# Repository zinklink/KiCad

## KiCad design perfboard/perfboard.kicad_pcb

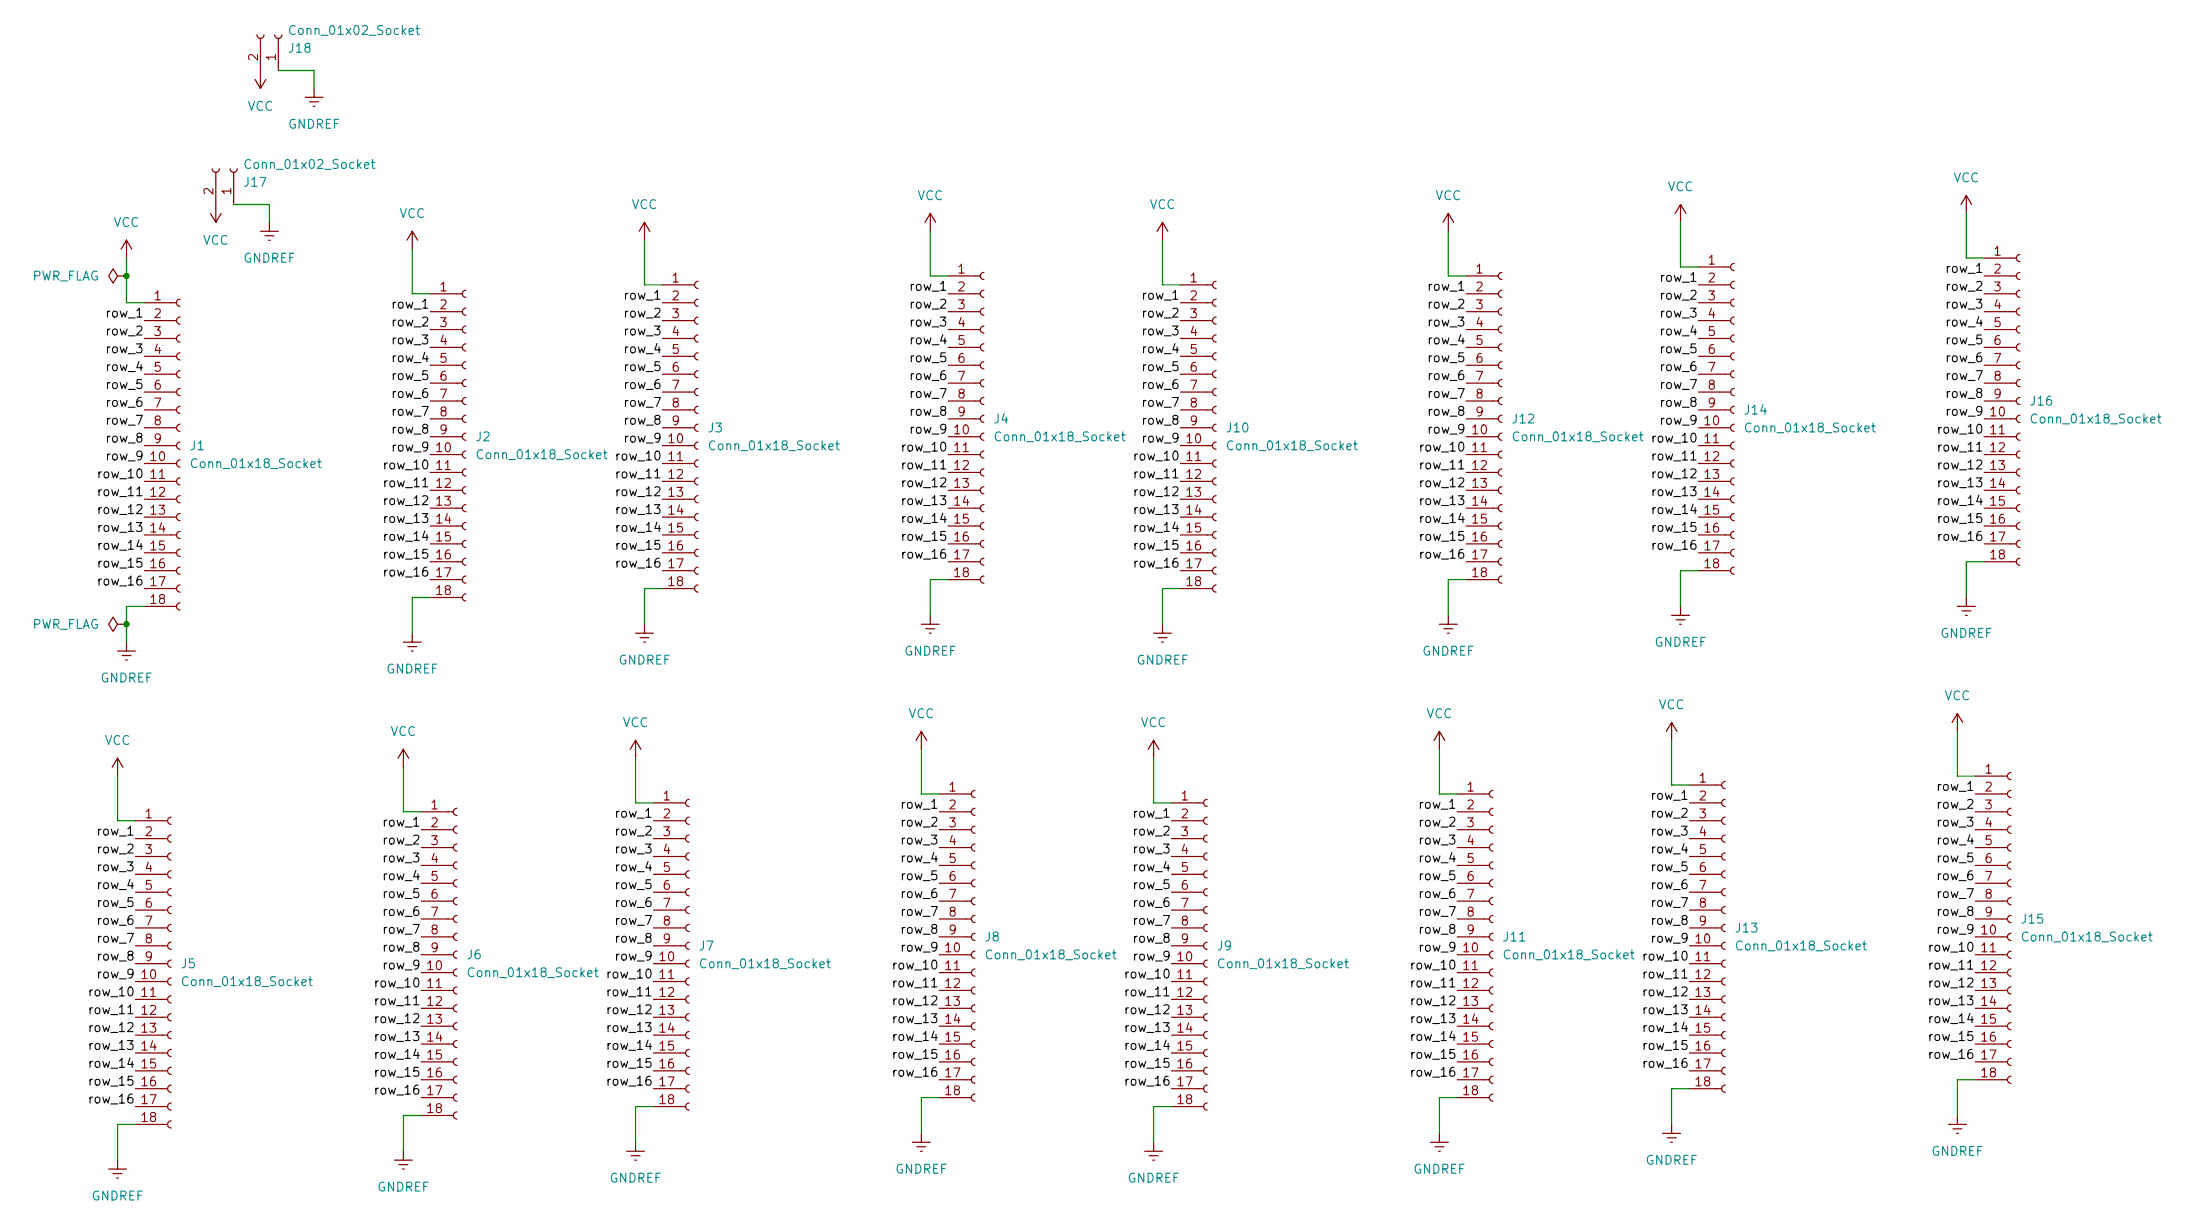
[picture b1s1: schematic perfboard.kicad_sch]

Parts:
J1, J2, J3, J4, J5, J6, J7, J8, J9, J10, J11, J12, J13, J14, J15, J16: Conn_01x18_Socket; PinHeader_1x18_P2.54mm_Vertical
J17, J18: Conn_01x02_Socket; PinHeader_1x02_P2.54mm_Vertical

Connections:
/row_1: J1.2, J2.2, J3.2, J4.2, J5.2, J6.2, J7.2, J8.2, J9.2, J10.2, J11.2, J12.2, J13.2, J14.2, J15.2, J16.2
/row_2: J1.3, J2.3, J3.3, J4.3, J5.3, J6.3, J7.3, J8.3, J9.3, J10.3, J11.3, J12.3, J13.3, J14.3, J15.3, J16.3
/row_3: J1.4, J2.4, J3.4, J4.4, J5.4, J6.4, J7.4, J8.4, J9.4, J10.4, J11.4, J12.4, J13.4, J14.4, J15.4, J16.4
/row_4: J1.5, J2.5, J3.5, J4.5, J5.5, J6.5, J7.5, J8.5, J9.5, J10.5, J11.5, J12.5, J13.5, J14.5, J15.5, J16.5
/row_5: J1.6, J2.6, J3.6, J4.6, J5.6, J6.6, J7.6, J8.6, J9.6, J10.6, J11.6, J12.6, J13.6, J14.6, J15.6, J16.6
/row_6: J1.7, J2.7, J3.7, J4.7, J5.7, J6.7, J7.7, J8.7, J9.7, J10.7, J11.7, J12.7, J13.7, J14.7, J15.7, J16.7
/row_7: J1.8, J2.8, J3.8, J4.8, J5.8, J6.8, J7.8, J8.8, J9.8, J10.8, J11.8, J12.8, J13.8, J14.8, J15.8, J16.8
/row_8: J1.9, J2.9, J3.9, J4.9, J5.9, J6.9, J7.9, J8.9, J9.9, J10.9, J11.9, J12.9, J13.9, J14.9, J15.9, J16.9
/row_9: J1.10, J2.10, J3.10, J4.10, J5.10, J6.10, J7.10, J8.10, J9.10, J10.10, J11.10, J12.10, J13.10, J14.10, J15.10, J16.10
/row_10: J1.11, J2.11, J3.11, J4.11, J5.11, J6.11, J7.11, J8.11, J9.11, J10.11, J11.11, J12.11, J13.11, J14.11, J15.11, J16.11
/row_11: J1.12, J2.12, J3.12, J4.12, J5.12, J6.12, J7.12, J8.12, J9.12, J10.12, J11.12, J12.12, J13.12, J14.12, J15.12, J16.12
/row_12: J1.13, J2.13, J3.13, J4.13, J5.13, J6.13, J7.13, J8.13, J9.13, J10.13, J11.13, J12.13, J13.13, J14.13, J15.13, J16.13
/row_13: J1.14, J2.14, J3.14, J4.14, J5.14, J6.14, J7.14, J8.14, J9.14, J10.14, J11.14, J12.14, J13.14, J14.14, J15.14, J16.14
/row_14: J1.15, J2.15, J3.15, J4.15, J5.15, J6.15, J7.15, J8.15, J9.15, J10.15, J11.15, J12.15, J13.15, J14.15, J15.15, J16.15
/row_15: J1.16, J2.16, J3.16, J4.16, J5.16, J6.16, J7.16, J8.16, J9.16, J10.16, J11.16, J12.16, J13.16, J14.16, J15.16, J16.16
/row_16: J1.17, J2.17, J3.17, J4.17, J5.17, J6.17, J7.17, J8.17, J9.17, J10.17, J11.17, J12.17, J13.17, J14.17, J15.17, J16.17
GNDREF: J1.18, J2.18, J3.18, J4.18, J5.18, J6.18, J7.18, J8.18, J9.18, J10.18, J11.18, J12.18, J13.18, J14.18, J15.18, J16.18, J17.1, J18.1
VCC: J1.1, J2.1, J3.1, J4.1, J5.1, J6.1, J7.1, J8.1, J9.1, J10.1, J11.1, J12.1, J13.1, J14.1, J15.1, J16.1, J17.2, J18.2

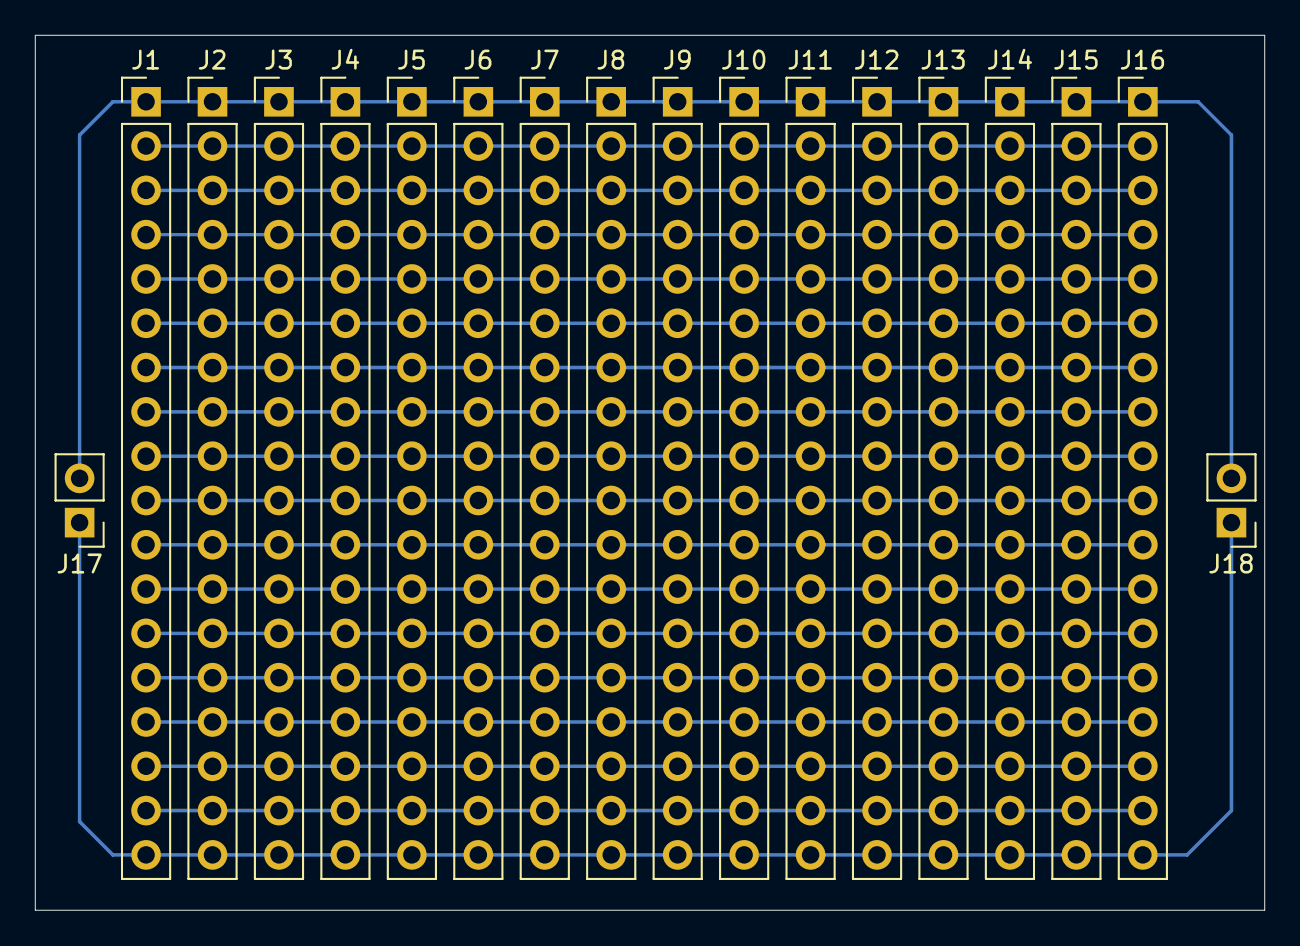
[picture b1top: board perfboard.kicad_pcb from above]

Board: 2 copper layers, 70.5 x 50.2 mm, 18 parts (0 on the bottom side), 18 nets.

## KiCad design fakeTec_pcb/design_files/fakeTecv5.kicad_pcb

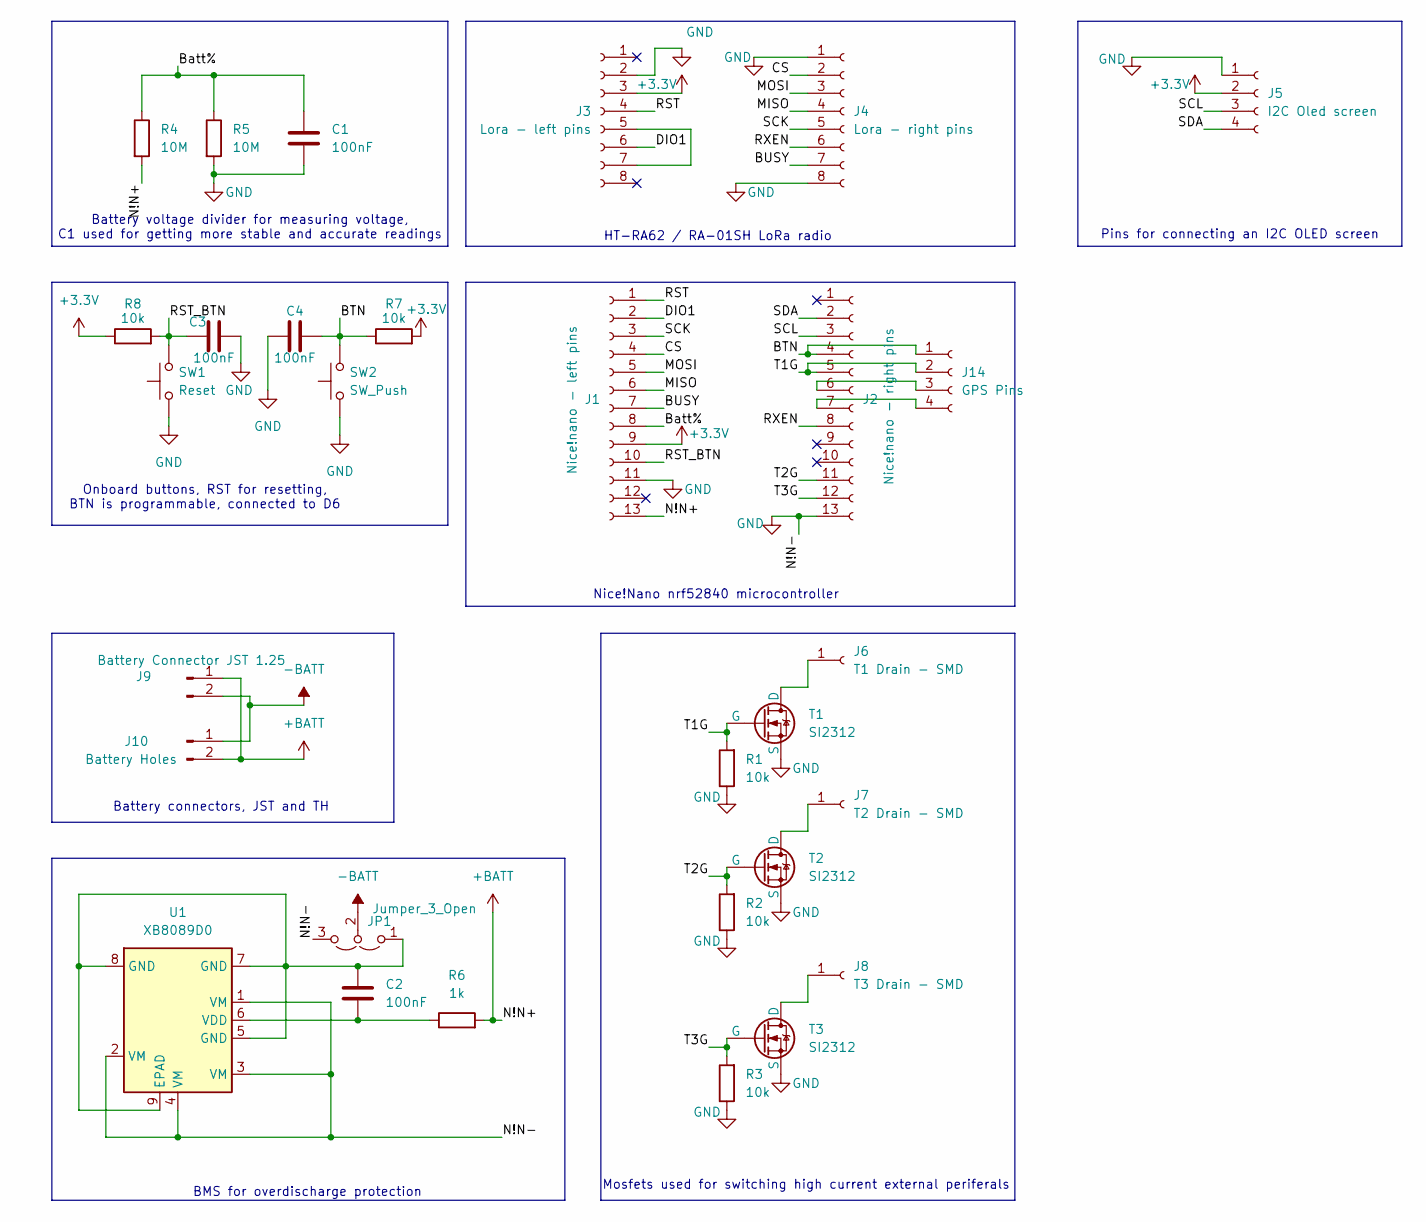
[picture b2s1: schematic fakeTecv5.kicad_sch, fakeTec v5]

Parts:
C1, C2, C3, C4: 100nF; C_1206_3216Metric_Pad1.33x1.80mm_HandSolder
J1: Nice!nano - left pins; SMD_Pad_Row_P2.54_13x1
J2: Nice!nano - right pins; SMD_Pad_Row_P2.54_13x1
J3: Lora - left pins; SMD_Pad_Row_P2.00_8x1_longer
J4: Lora - right pins; SMD_Pad_Row_P2.00_8x1
J5: I2C Oled screen; PinHeader_1x04_P2.54mm_Vertical
J6: T1 Drain - SMD; SMD_PAD_1x1
J7: T2 Drain - SMD; SMD_PAD_1x1
J8: T3 Drain - SMD; SMD_PAD_1x1
J9: Battery Connector JST 1.25; JST_GH_SM02B-GHS-TB_1x02-1MP_P1.25mm_Horizontal
J10: Battery Holes; PinHeader_1x02_P2.54mm_Vertical
J14: GPS Pins; SMD_PAD_4x1
JP1: Jumper_3_Open; SolderJumper-3_P1.3mm_Open_RoundedPad1.0x1.5mm
R1, R2, R3, R7, R8: 10k; R_1206_3216Metric_Pad1.30x1.75mm_HandSolder
R4, R5: 10M; R_1206_3216Metric_Pad1.30x1.75mm_HandSolder
R6: 1k; R_1206_3216Metric_Pad1.30x1.75mm_HandSolder
SW1: Reset; SW_Push_SPST_NO_Alps_SKRK
SW2: SW_Push; SW_Push_SPST_NO_Alps_SKRK
T1, T2, T3: SI2312; TSOT-23_HandSoldering_Updated
U1: XB8089D0; SOIC-8-1EP_3.9x4.9mm_P1.27mm_EP2.41x3.3mm

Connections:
+3.3V: J1.9, J3.3, J5.2, R7.2, R8.1
+BATT: J1.13, J9.1, J10.2, R4.2, R6.2
-BATT: J9.2, J10.1, JP1.2 (C)
/BTN: C4.2, J2.4, J14.1, R7.1, SW2.2
/BUSY: J1.7, J4.7
/Batt%: C1.1, J1.8, R4.1, R5.1
/CS: J1.4, J4.2
/DIO1: J1.2, J3.6
/MISO: J1.6, J4.4
/MOSI: J1.5, J4.3
/RST: J1.1, J3.4
/RST_BTN: C3.1, J1.10, R8.2, SW1.2
/RXEN: J2.8, J4.6
/SCK: J1.3, J4.5
/SCL: J2.3, J5.3
/SDA: J2.2, J5.4
/T1G: J2.5, J14.2, R1.2, T1.2 (G)
/T2G: J2.11, R2.2, T2.2 (G)
/T3G: J2.12, R3.2, T3.2 (G)
GND: C1.2, C3.2, C4.1, J1.11, J2.13, J3.2, J4.1, J4.8, J5.1, JP1.3 (B), R1.1, R2.1, R3.1, R5.2, SW1.1, SW2.1, T1.3 (S), T2.3 (S), T3.3 (S), U1.1 (VM), U1.2 (VM), U1.3 (VM), U1.4 (VM)
unnamed: J3.5, J3.7
unnamed: J6.1, T1.1 (D)
unnamed: J7.1, T2.1 (D)
unnamed: J8.1, T3.1 (D)
unnamed: J2.6, J14.3
unnamed: J2.7, J14.4
unnamed: C2.1, JP1.1 (A), U1.5 (GND), U1.7 (GND), U1.8 (GND), U1.9 (EPAD)
unnamed: C2.2, R6.1, U1.6 (VDD)

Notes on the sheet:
Nice!Nano nrf52840 microcontroller
Mosfets used for switching high current external periferals
BMS for overdischarge protection
Battery voltage divider for measuring voltage, C1 used for getting more stable and accurate readings
HT-RA62 / RA-01SH LoRa radio
Onboard buttons, RST for resetting, BTN is programmable, connected to D6
Battery connectors, JST and TH
Pins for connecting an I2C OLED screen

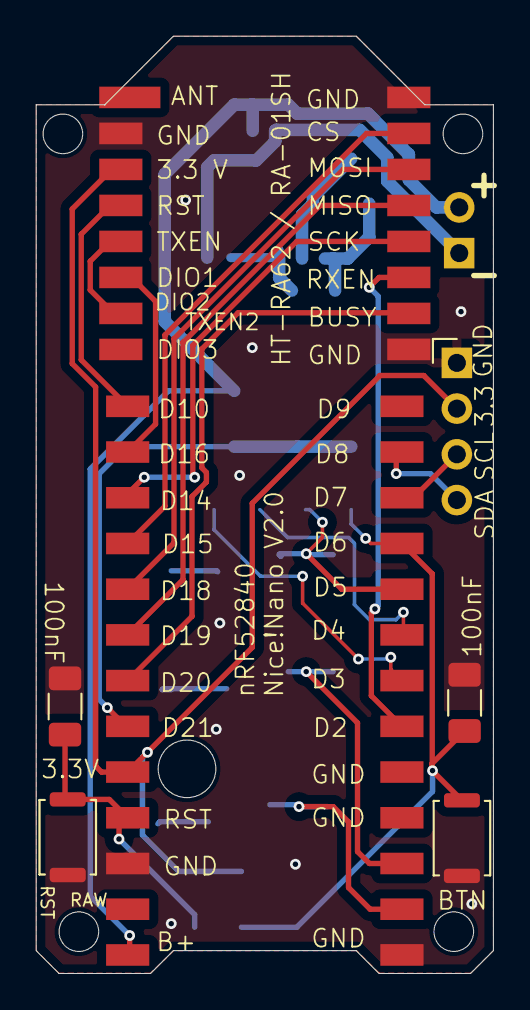
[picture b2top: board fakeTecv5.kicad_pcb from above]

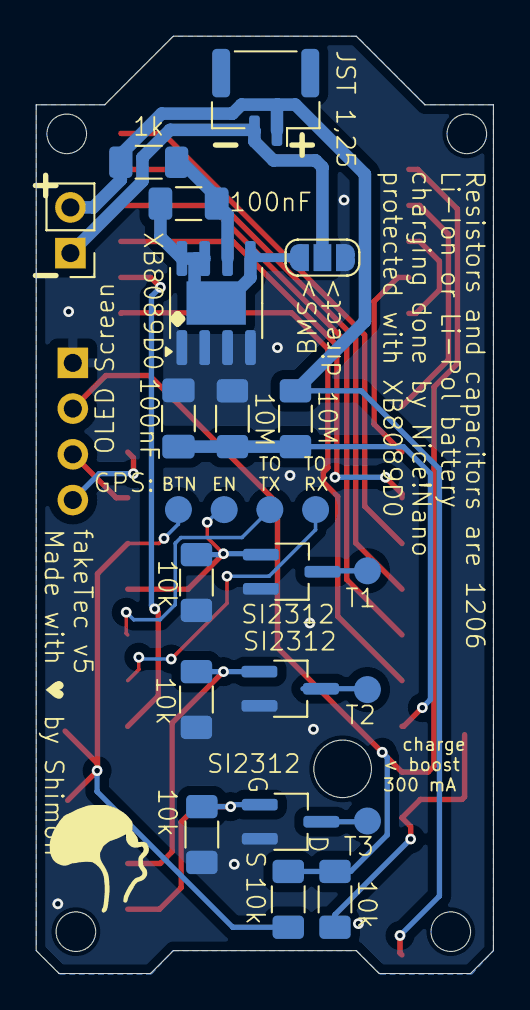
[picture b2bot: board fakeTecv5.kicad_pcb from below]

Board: 2 copper layers, 25.4 x 52.1 mm, 30 parts (21 on the bottom side), 28 nets.

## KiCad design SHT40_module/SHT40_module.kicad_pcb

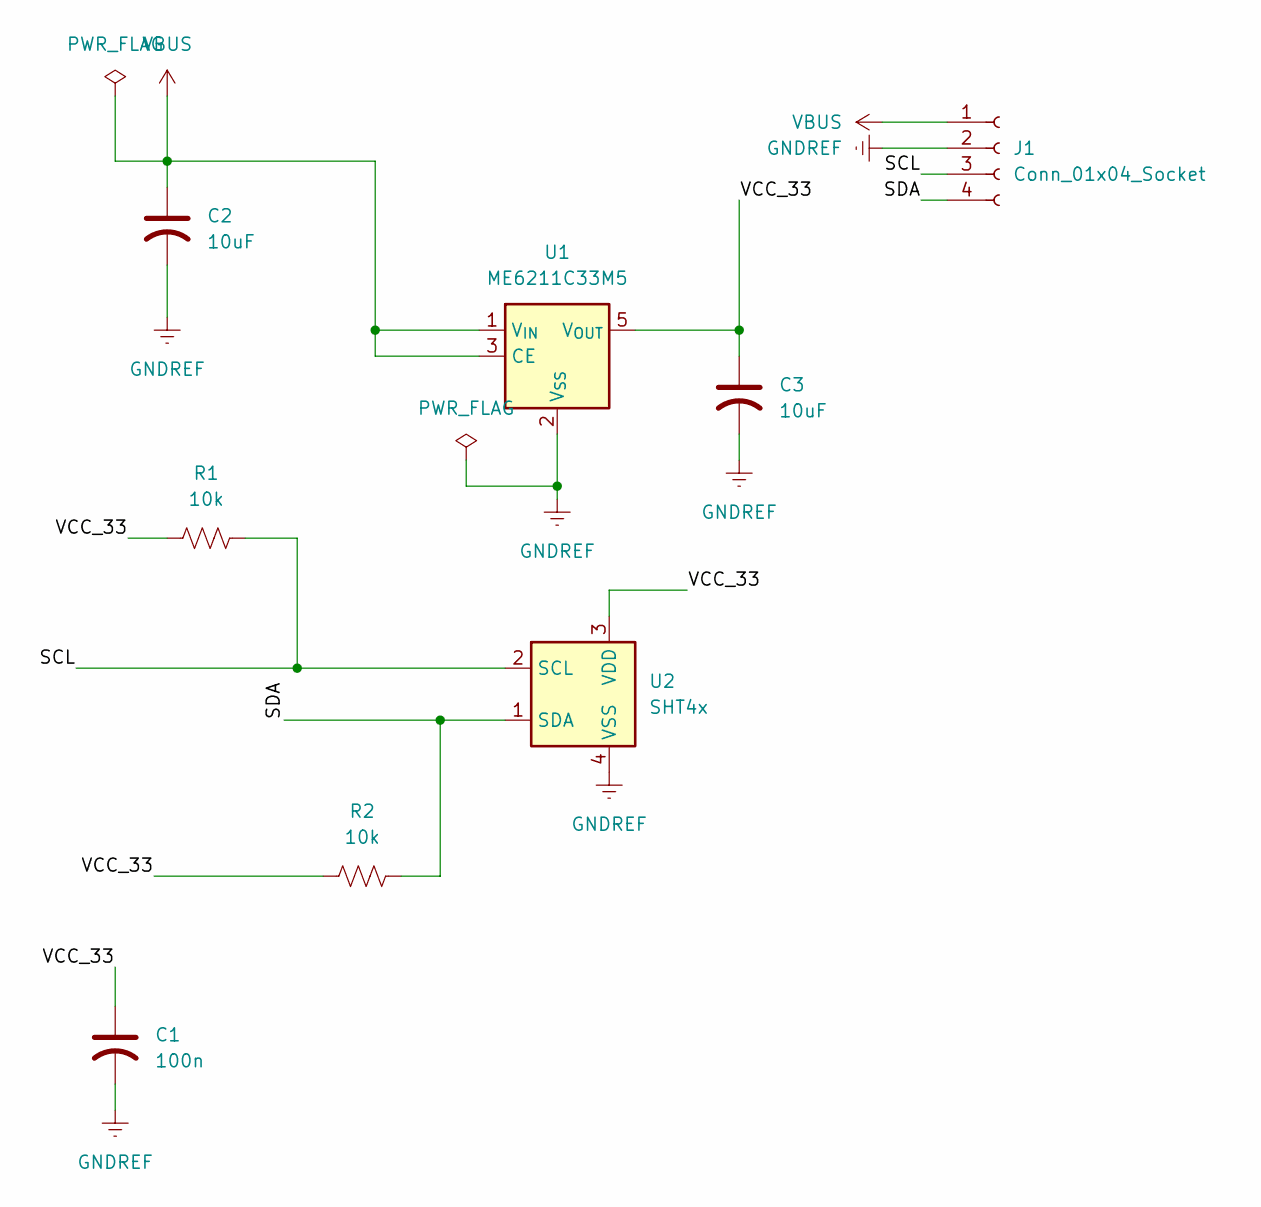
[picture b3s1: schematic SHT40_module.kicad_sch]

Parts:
C1: 100n; C_1206_3216Metric_Pad1.33x1.80mm_HandSolder
C2, C3: 10uF; C_1206_3216Metric_Pad1.33x1.80mm_HandSolder
J1: Conn_01x04_Socket; PinHeader_1x04_P1.00mm_Horizontal
R1, R2: 10k; R_1206_3216Metric_Pad1.30x1.75mm_HandSolder
U1: ME6211C33M5; SOT-23-5
U2: SHT4x; Sensirion_DFN-4_1.5x1.5mm_P0.8mm_SHT4x_NoCentralPad

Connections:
/SCL: J1.3, R1.2, U2.2 (SCL)
/SDA: J1.4, R2.2, U2.1 (SDA)
/VCC_33: C1.1, C3.1, R1.1, R2.1, U1.5 (V_{OUT}), U2.3 (VDD)
GNDREF: C1.2, C2.2, C3.2, J1.2, U1.2 (V_{SS}), U2.4 (VSS)
VBUS: C2.1, J1.1, U1.1 (V_{IN}), U1.3 (CE)

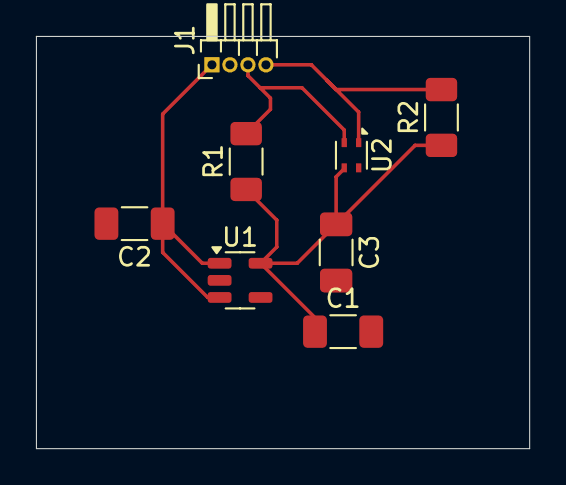
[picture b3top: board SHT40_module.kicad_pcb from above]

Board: 2 copper layers, 27.4 x 22.9 mm, 8 parts (0 on the bottom side), 5 nets.

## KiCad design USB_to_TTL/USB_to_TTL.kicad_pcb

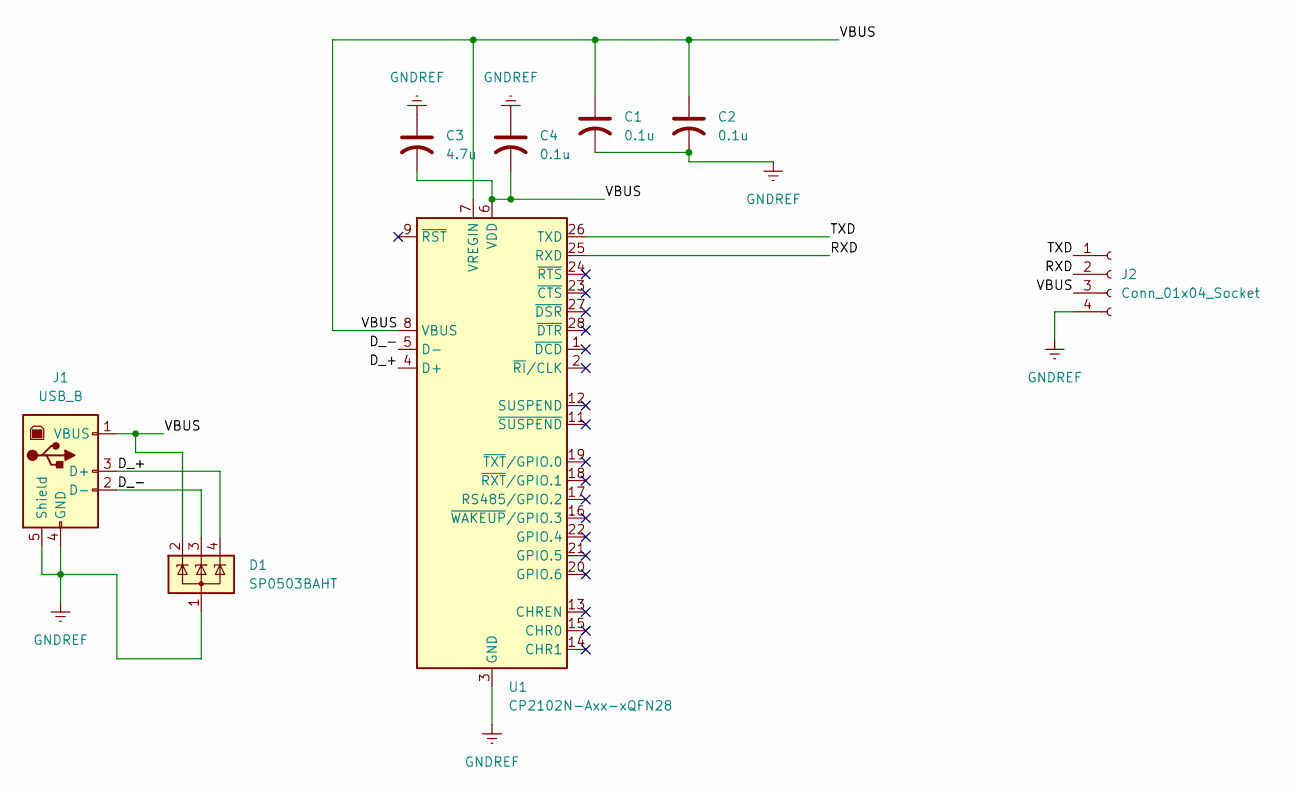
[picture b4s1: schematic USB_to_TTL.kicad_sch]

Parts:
C1, C2, C4: 0.1u; C_0603_1608Metric_Pad1.08x0.95mm_HandSolder
C3: 4.7u; C_0603_1608Metric_Pad1.08x0.95mm_HandSolder
D1: SP0503BAHT; SOT-143
J1: USB_B; USB_B_TE_5787834_Vertical
J2: Conn_01x04_Socket; PinSocket_1x04_P2.54mm_Vertical
U1: CP2102N-Axx-xQFN28; QFN-28-1EP_5x5mm_P0.5mm_EP3.35x3.35mm

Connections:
/D_+: D1.4 (K), J1.3 (D+), U1.4 (D+)
/D_-: D1.3 (K), J1.2 (D-), U1.5 (D-)
/RXD: J2.2, U1.25 (RXD)
/TXD: J2.1, U1.26 (TXD)
/VBUS: C1.1, C2.1, C3.2, C4.2, D1.2 (K), J1.1 (VBUS), J2.3, U1.6 (VDD), U1.7 (VREGIN), U1.8 (VBUS)
GNDREF: C1.2, C2.2, C3.1, C4.1, D1.1 (A), J1.4 (GND), J1.5 (Shield), J2.4, U1.3 (GND), U1.29 (GND)

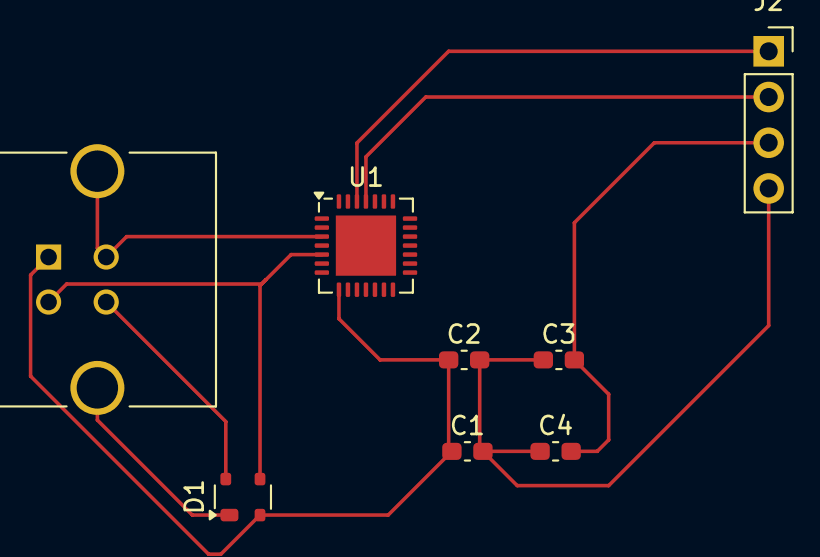
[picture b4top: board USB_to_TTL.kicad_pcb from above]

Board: 2 copper layers, 8 parts (0 on the bottom side), 6 nets.

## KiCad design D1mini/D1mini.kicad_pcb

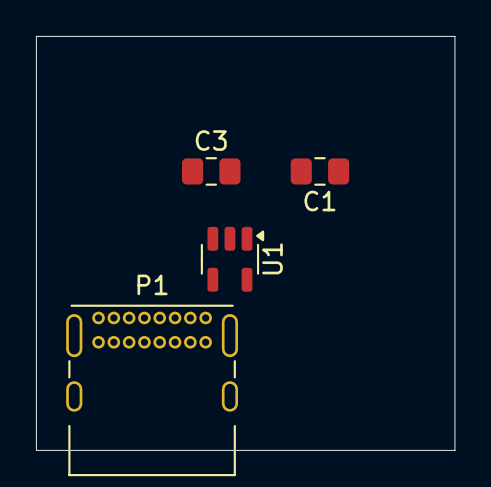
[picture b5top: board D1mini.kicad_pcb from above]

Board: 2 copper layers, 23.2 x 23.0 mm, 4 parts (0 on the bottom side), 3 nets, no tracks yet.

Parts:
C1, C3: 1u; C_0805_2012Metric_Pad1.18x1.45mm_HandSolder
P1: USB_C_Plug_USB2.0; USB_C_Receptacle_GCT_USB4085
U1: ME6211C33M5; SOT-23-5

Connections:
+5Vfe: C3.1, P1.A4 (VBUS), P1.A9 (VBUS), P1.B4 (VBUS), P1.B9 (VBUS), U1.1 (V_{IN}), U1.3 (CE)
/+3V3: C1.1, U1.5 (V_{OUT})
GNDREF: C1.2, C3.2, P1.A1 (GND), P1.A12 (GND), P1.B1 (GND), P1.B12 (GND), P1.S1 (SHIELD), U1.2 (V_{SS})

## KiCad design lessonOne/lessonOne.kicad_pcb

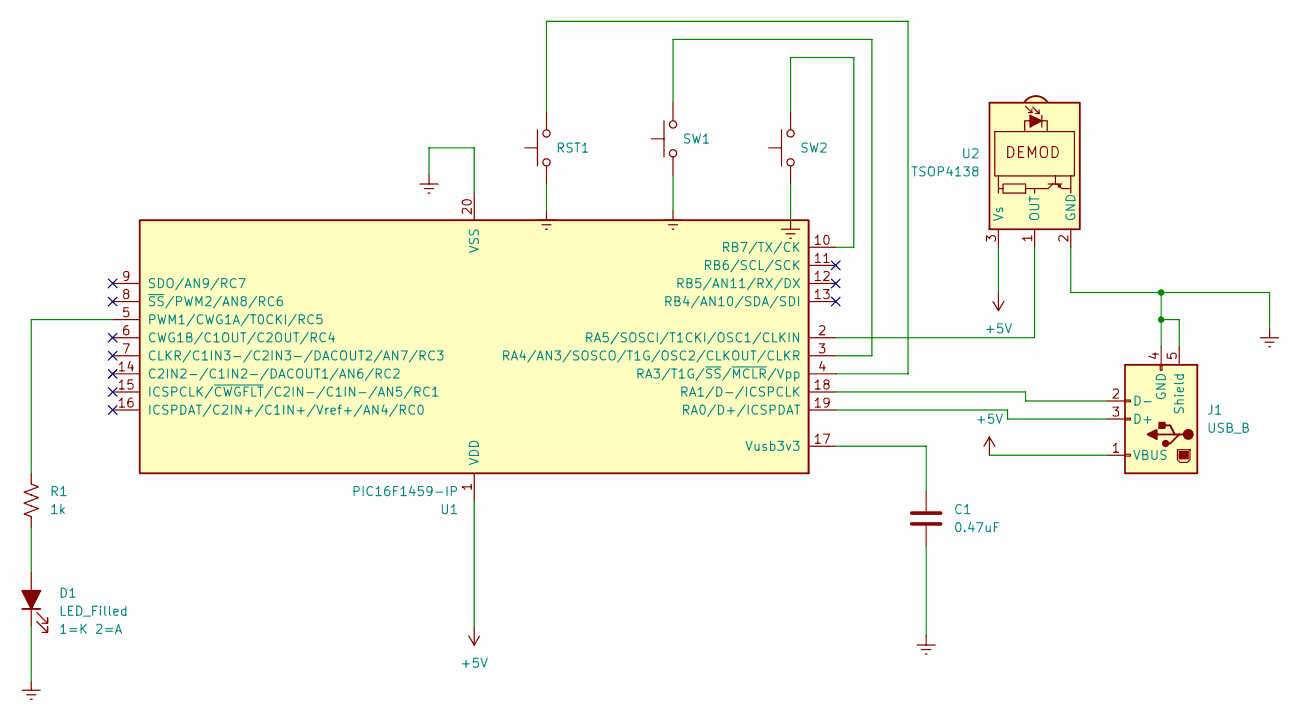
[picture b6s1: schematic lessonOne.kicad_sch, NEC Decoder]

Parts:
C1: 0.47uF; C_Disc_D4.3mm_W1.9mm_P5.00mm
D1: LED_Filled; LED_D3.0mm
J1: USB_B; USB_B_Lumberg_2411_02_Horizontal
R1: 1k; R_Axial_DIN0207_L6.3mm_D2.5mm_P10.16mm_Horizontal
RST1: SW_Push; SW_PUSH_6mm
SW1, SW2: SW_Push; SW_PUSH_6mm
U1: PIC16F1459-IP; DIP-20_W7.62mm_LongPads
U2: TSOP4138; Vishay_MOLD-3Pin

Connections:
+5V: J1.1 (VBUS), U1.1 (VDD), U2.3 (Vs)
GNDREF: C1.2, D1.1 (K), J1.4 (GND), J1.5 (Shield), RST1.1, SW1.1, SW2.1, U1.20 (VSS), U2.2 (GND)
unnamed: D1.2 (A), R1.2
unnamed: J1.3 (D+), U1.19 (RA0/D+/ICSPDAT)
unnamed: J1.2 (D-), U1.18 (RA1/D-/ICSPCLK)
unnamed: R1.1, U1.5 (PWM1/CWG1A/T0CKI/RC5)
unnamed: RST1.2, U1.4 (RA3/T1G/~SS/~MCLR/Vpp)
unnamed: SW1.2, U1.3 (RA4/AN3/SOSCO/T1G/OSC2/CLKOUT/CLKR)
unnamed: U1.2 (RA5/SOSCI/T1CKI/OSC1/CLKIN), U2.1 (OUT)
unnamed: SW2.2, U1.10 (RB7/TX/CK)
unnamed: C1.1, U1.17 (Vusb3v3)

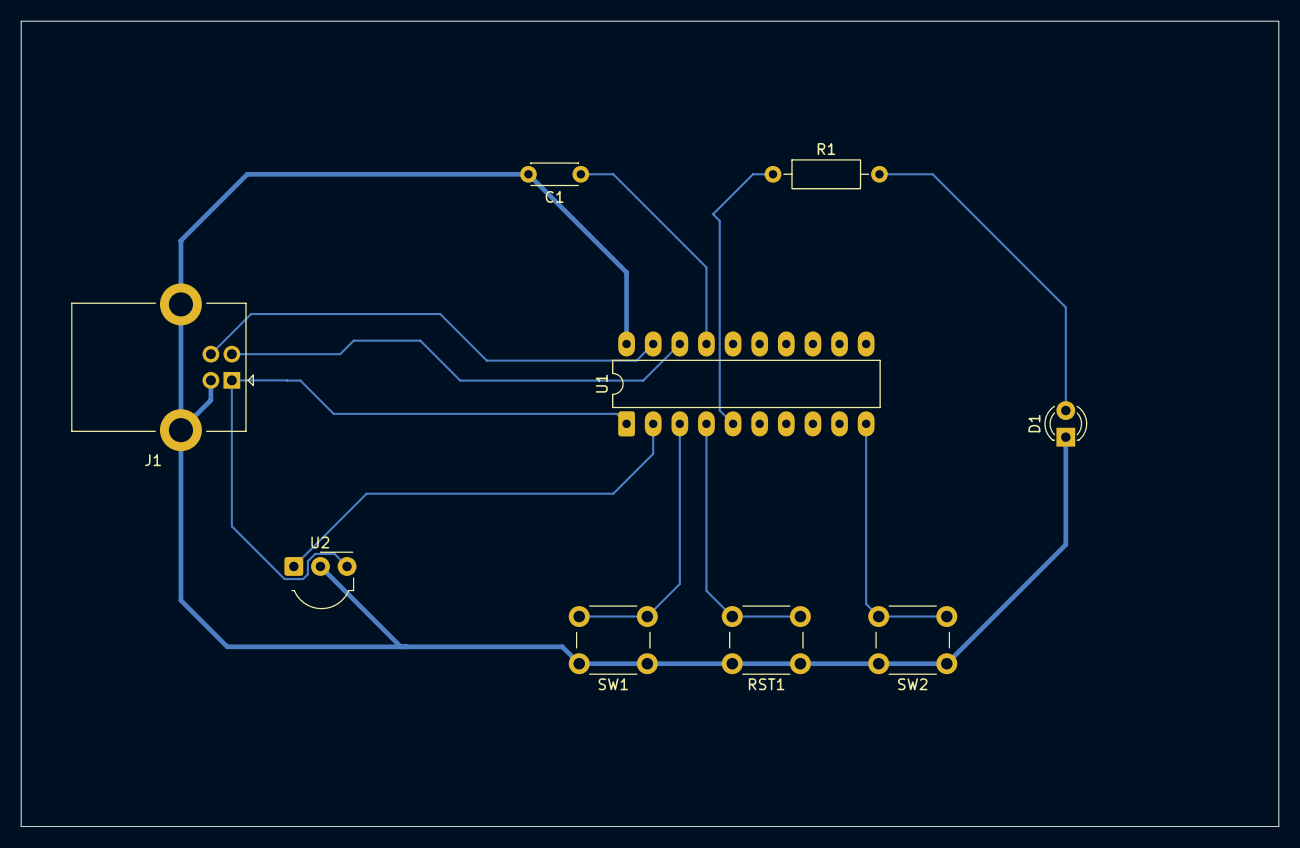
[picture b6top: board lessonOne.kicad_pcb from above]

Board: 2 copper layers, 120.0 x 76.8 mm, 9 parts (0 on the bottom side), 11 nets.

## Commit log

2025-08-04 調整.gitignore的內容
2025-08-06 add I2C bus project
2025-08-06 新增BEM280
2025-08-06 繼續編輯
2025-08-07 20250807 modify
2025-08-08 新增新專案, usb to TTL
2025-08-08 add cp2919
2025-08-11 繼續作圖
2025-08-13 完成PCB佈線
2025-08-26 add usb jiggler
2025-08-26 完成mouse jiggler
2025-09-19 add SHT40 sensor module
2025-09-21 add perfboard
